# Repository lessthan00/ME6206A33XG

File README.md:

# ME6206A33XG  borad change from AMS1117-3V3

[ME6206A33XG](https://www.jlc-smt.com/lcsc/detail?componentCode=C161345)  
LDO  
VIN 6V  
VOUT 3.3V  
IOUT 300mA  
pakcage SOT-23-3  
IQ 8uA  
VD 400mV@200mA  

引脚定义  
1-GND  
2-VOUT  
3-VIN  

kciad 并无其符号, 根据封装和引脚定义, 选择自MCP1703Ax-330xxTT 这个符号派生  
封装也是取其 Package_TO_SOT_SMD:SOT-23  
输入TVS 改为 SMAJ6.0CA  
  
## AMS1117-3V3  borad change from HT7333
  
[AMS1117-3V3](https://www.jlc-smt.com/lcsc/detail?componentCode=C5120765)  
LDO  
  
VIN 18V  
VOUT 3.3V  
IOUT 1A  
package SOT-223  
IQ 12mA  
VD 1.4V@1A  
  
引脚引脚定义  
  
1 GND  
2 VOUT  
3 VIN  

输入TVS 改为SMAJ18CA
  
## HT7333  
  
[HT7333](https://item.szlcsc.com/323851.html?fromZone=s_s__%2522HT7333%2522&spm=sc.gb.xh2.zy.n___sc.hm.hd.ss&lcsc_vid=EwQKBQVXRFYIBQVTR1JbVFcAFgRYUl0AFFNZVAEARVQxVlNSQVZWVVFfRVBZXzsOAxUeFF5JWBYZEEoEHg8JSQcJGk4%3D)  
  
LDO  
  
VIN 12V  
VOUT 3.3V  
IOUT 250mA  
package SOT-89-3  
IQ 3uA  
VD 90mV@40mA  
  
引脚定义  
  
1 GND  
2 VIN  
3 VOUT  
  
所以使用kciad 里面的 Regulator_Generic_GND_IN_OUT 生成符号  
  
封装采用PCM_Package_TO_SOT_SMD_AKL:SOT-89-3, 已确认封装焊盘顺序定义无误  
  
## TLV70450DBVR  
  
[TLV70450DBVR](https://www.jlc-smt.com/lcsc/detail?componentCode=C91672)  
VIN 24V  
VOUT 5V  
IOUT 150mA  
IQ 4.5uA  
VD 1.1V@100mA  
package SOT-23-5  
  
1-GND  
2-IN  
3-OUT  
4-NC  
5-NC  
  
这样的封装的引脚定义是很少的,基本上只有TLV70450DBVR,甚至需要自己绘制封装...

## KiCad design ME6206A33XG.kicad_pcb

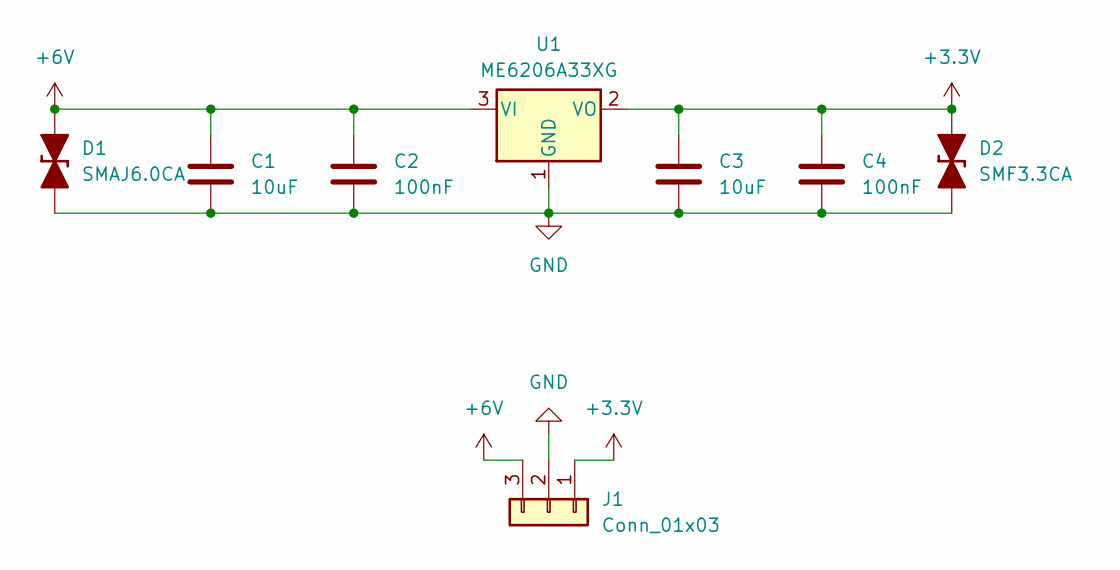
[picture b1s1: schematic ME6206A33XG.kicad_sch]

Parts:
C1, C3: 10uF; C_1206_3216Metric
C2, C4: 100nF; C_1206_3216Metric
D1: SMAJ6.0CA; D_SMA_TVS
D2: SMF3.3CA; D_SOD-123F
J1: Conn_01x03; PinHeader_1x03_P2.54mm_Vertical
U1: ME6206A33XG; SOT-23

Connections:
+3.3V: C3.1, C4.1, D2.2 (A), J1.1, U1.2 (VO)
+6V: C1.1, C2.1, D1.2 (A), J1.3, U1.3 (VI)
GND: C1.2, C2.2, C3.2, C4.2, D1.1 (K), D2.1 (K), J1.2, U1.1 (GND)

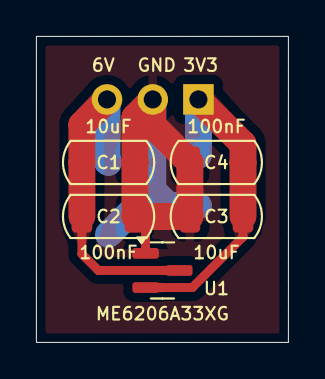
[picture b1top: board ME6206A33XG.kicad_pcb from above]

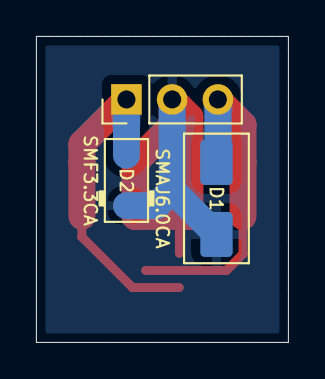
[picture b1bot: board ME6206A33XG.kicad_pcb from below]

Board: 2 copper layers, 14.0 x 17.0 mm, 8 parts (3 on the bottom side), 3 nets.
